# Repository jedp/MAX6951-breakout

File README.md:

# MAX6950/6951 Breakout
## 5- and 8-digit LED display drivers

A board for mounting [MAX6950 and
MAX6951](https://www.digikey.com/en/products/detail/inolux/IN-PI554FCH/7604874)
LED display drivers.

Note that this chip has a thermal relief slug on the underside.

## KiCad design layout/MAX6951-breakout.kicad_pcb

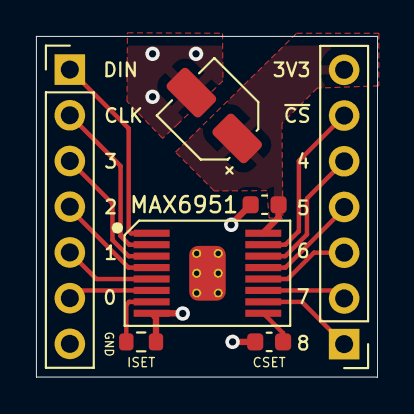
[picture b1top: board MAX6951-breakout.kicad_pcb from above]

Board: 2 copper layers, 18.9 x 18.9 mm, 7 parts (0 on the bottom side), 16 nets.

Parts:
C1: 22u; CP_Elec_4x3
C2: 0.1u; C_0603_1608Metric
C3: 27pF; C_0603_1608Metric
J1, J2: Conn_01x07_Female; PinHeader_1x07_P2.54mm_Vertical
MAX6951: MAX6951_ThermalVias
R1: 56k; R_0603_1608Metric

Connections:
+3V3: C1.1, C2.1, J2.7, MAX6951.16 (VCC)
CLK: J1.2, MAX6951.2 (CLK)
DIN: J1.1, MAX6951.1 (DIN)
GND: C1.2, C2.2, C3.2, J1.7, MAX6951.8 (GND), MAX6951.17 (GND), R1.2
ISET: MAX6951.7 (ISET), R1.1
OSC: C3.1, MAX6951.9 (OSC)
SEG0: J1.6, MAX6951.6 (DIG0/SEG0)
SEG1: J1.5, MAX6951.5 (DIG1/SEG1)
SEG2: J1.4, MAX6951.4 (DIG2/SEG2)
SEG3: J1.3, MAX6951.3 (DIG3/SEG3)
SEG4: J2.5, MAX6951.14 (DIG4/SEG4)
SEG5: J2.4, MAX6951.13 (DIG5/SEG5)
SEG6: J2.3, MAX6951.12 (DIG6/SEG6)
SEG7: J2.2, MAX6951.11 (DIG7/SEG7)
SEG8: J2.1, MAX6951.10 (SEG8)
~CS: J2.6, MAX6951.15 (~CS)

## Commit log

2021-02-08 MAX6951
2022-12-30 Update schematic and PCB to include thermal pad
2023-01-16 Correct board layout of ISET
    See Board Layout on datasheet page 16 and Figure 5.
2023-01-22 Fix crucial typo
